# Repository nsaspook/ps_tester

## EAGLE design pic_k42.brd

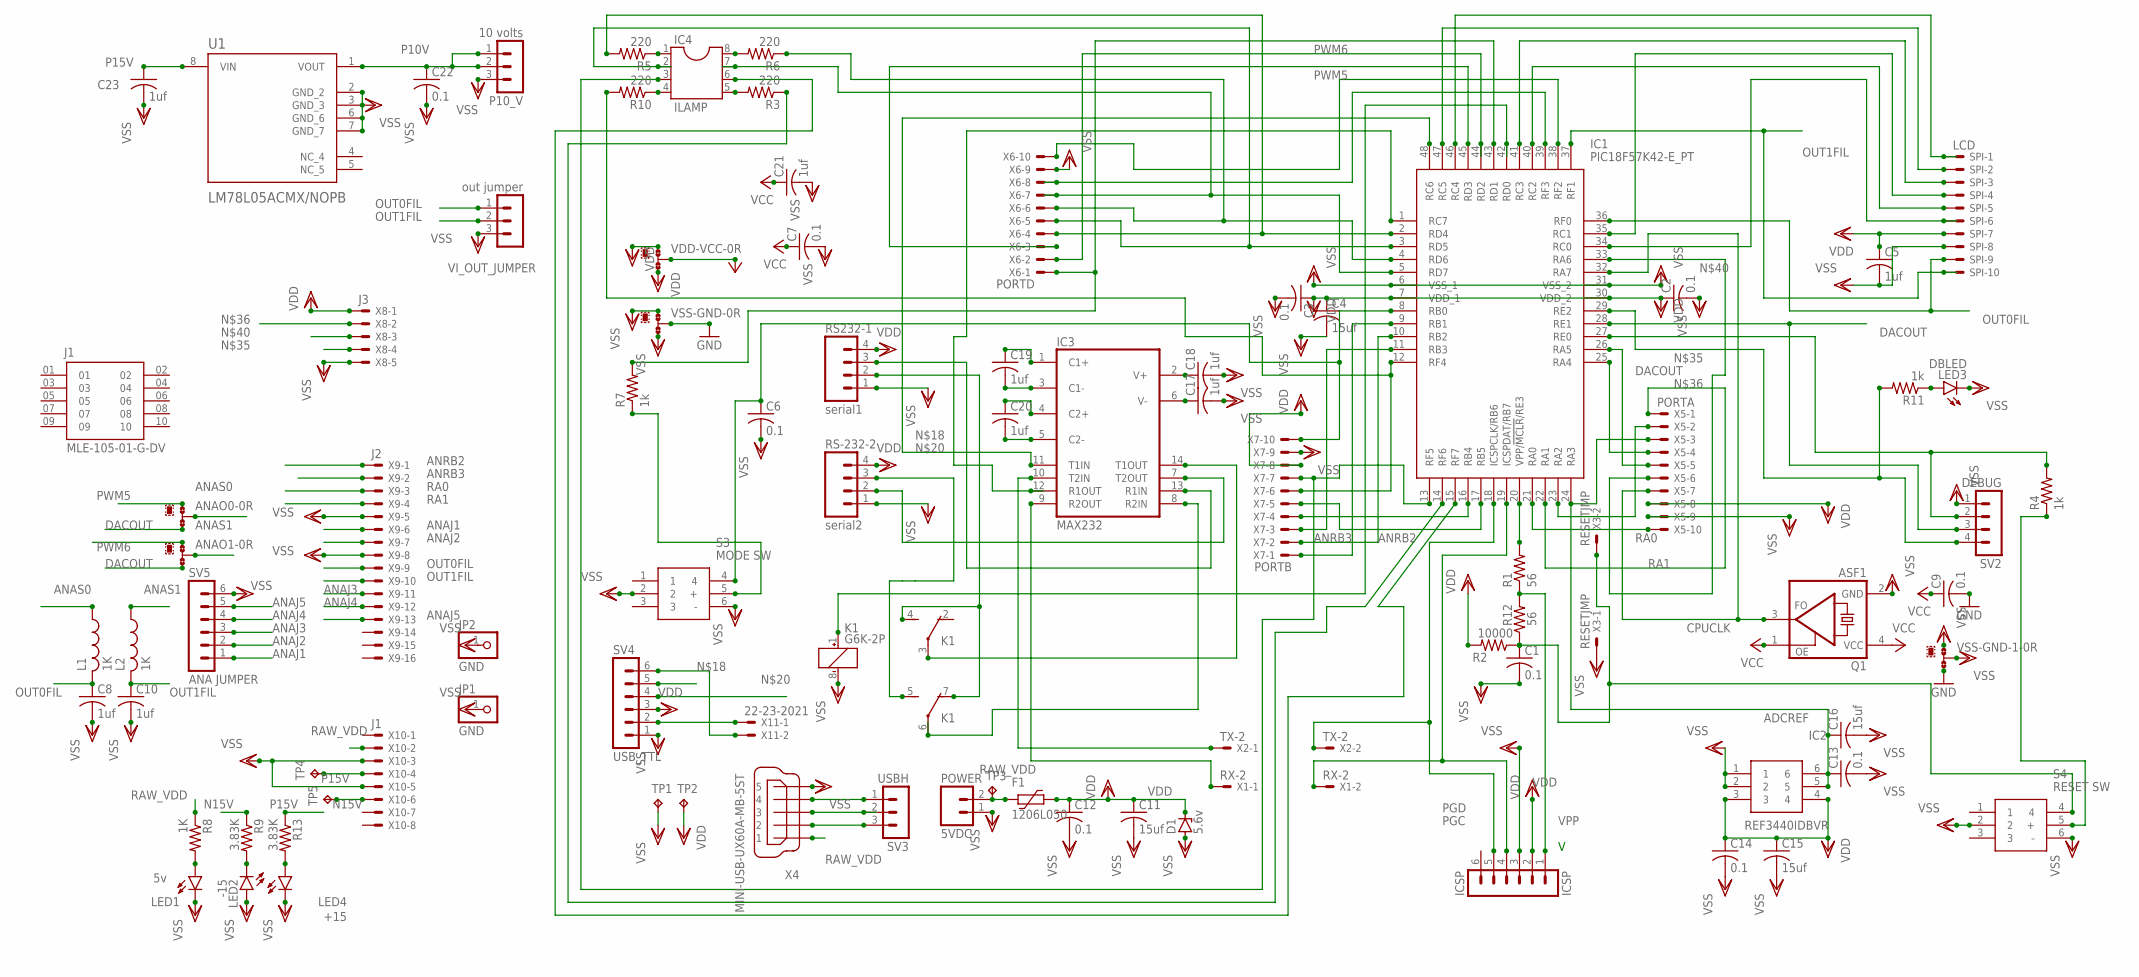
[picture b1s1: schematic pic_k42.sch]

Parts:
ANAO0: PS V; A0R-JMP
ANAO1: PS I; A0R-JMP
C1, C2, C3, C6, C7, C9, C12, C13, C14, C22: 0.1; C1206
C4, C11, C15, C16: 15uf; C1206
C5, C8, C10, C17, C18, C19, C20, C21, C23: 1uf; C0805
D1: 5.6v; DO34Z7
F1: 1206L050; 1206L
IC1: PIC18F57K42-E_PT; QFP50P900X900X120-48N
IC2: REF3440IDBVR; SOP95P280X145-6N
IC3: MAX232; DIL16
IC4: ILAMP; SOCKET-08
ICSP: ICSP; MA06-1
J1: MLE-105-01-G-DV; SAMTEC_MLE-105-01-G-DV
JP1, JP2: GND; 1X01
K1: G6K-2P
L1, L2: 1K; L2012C
LED1: 5v; CHIPLED_1206
LED2: -15; CHIPLED_1206
LED3: DBLED; CHIPLED_1206
LED4: +15; CHIPLED_1206
P10_V: 10 volts; MA03-1
POWER: 5VDC; 02P
Q1: ASF1; ASF
R1, R12: 56; R1206
R2: 10000; R1206
R3, R5, R6, R10: 220; R1206
R4, R7, R11: 1k; R1206
R8: 1K; R1206
R9, R13: 3.83K; R1206
RS232-1: serial1; 04P
RS-232-2: serial2; 04P
S3: MODE SW; B3W-9_1-LED
S4: RESET SW; B3W-9_1-LED
SPI: LCD; 22-23-2101
SV2: DEBUG; MA04-1
SV3: USBH; MA03-1
SV4: USB_TTL; MA06-1
SV5: ANA JUMPER; MA06-1
TP1, TP2, TP3, TP4, TP5: TPB1,27; B1,27
U1: LM78L05ACMX/NOPB; SOIC127P599X175-8N
VDD-VCC: VDD-VCC; A0R-JMP
VI_OUT_JUMPER: out jumper; MA03-1
VSS-GND: VSS-GND; A0R-JMP
VSS-GND-1: 0R-JUMPA; A0R-JMP
X1: RX-2; 332-02
X2: TX-2; 332-02
X3: RESETJMP; 332-02
X4: MINI-USB-UX60A-MB-5ST; UX60A-MB-5ST
X5: PORTA; 22-23-2101
X6: PORTD; 22-23-2101
X7: PORTB; 22-23-2101
X8: J3; KK-156-5
X9: J2; KK-156-16
X10: J1; KK-156-8
X11: 22-23-2021

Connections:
ADCREF: C13.1, C16.1, IC1.24 (RA3), IC2.5, IC2.6, X5.3
ANAJ1: SV5.1, X9.6
ANAJ2: SV5.2, X9.7
ANAJ3: SV5.3, X9.11
ANAJ4: SV5.4, X9.12
ANAJ5: SV5.5, X9.13
ANAS0: ANAO0.2, L1.1
ANAS1: ANAO1.2, L2.1
ANRB2: IC1.10 (RB2), X7.2, X9.1
ANRB3: IC1.11 (RB3), X7.3, X9.2
CPUCLK: IC1.32 (RA7), Q1.3 (FO), X5.7
DACOUT: ANAO0.3, ANAO1.3, IC1.23 (RA2), IC1.28 (RE1), SV2.3, X5.2
GND: C9.2, IC3.15 (GND), VSS-GND.2, VSS-GND-1.3
N15V: R9.1, TP5.TP, X10.6
unnamed: IC1.20 (VPP/!MCLR!/RE3), R1.2
unnamed: IC4.1, R5.1
unnamed: C17.1, IC3.6 (V-)
unnamed: C18.1, IC3.2 (V+)
unnamed: C19.1, IC3.1 (C1+)
unnamed: C20.1, IC3.4 (C2+)
unnamed: C20.2, IC3.5 (C2-)
unnamed: C19.2, IC3.3 (C1-)
unnamed: K1.4 (S), K1.7 (O), RS232-1.2
unnamed: IC3.7 (T2OUT), RS-232-2.2
unnamed: IC3.13 (R1IN), RS232-1.3
unnamed: IC4.8, R6.2
unnamed: IC1.1 (RC7), IC3.12 (R1OUT), SV4.5
unnamed: IC3.9 (R2OUT), X1.1
unnamed: IC1.48 (RC6), IC3.11 (T1IN), SV4.4
unnamed: R4.1, S4.5 (+)
unnamed: IC3.10 (T2IN), X2.1
unnamed: IC1.27 (RE0), R4.2, SV2.2
unnamed: IC1.29 (RE2), R11.2, SV2.4
unnamed: IC3.14 (T1OUT), K1.3
unnamed: IC3.8 (R2IN), K1.6
unnamed: IC1.42 (RD0), K1.1 (+)
unnamed: IC1.46 (RC4), SPI.1
unnamed: IC1.47 (RC5), SPI.2
unnamed: IC1.41 (RC3), SPI.3
unnamed: IC1.35 (RC1), SPI.4
unnamed: IC1.40 (RC2), SPI.5
unnamed: IC1.34 (RC0), SPI.6
unnamed: IC1.26 (RA5), X5.5, X8.4
unnamed: IC1.25 (RA4), X5.4, X8.2
unnamed: IC1.33 (RA6), X5.6, X8.3
unnamed: C6.1, IC1.8 (RB0), S3.4, X7.10
unnamed: IC1.45 (RD3), X6.3
unnamed: IC1.2 (RD4), R5.2, X6.4
unnamed: IC1.3 (RD5), IC4.2, X6.5
unnamed: IC1.4 (RD6), R6.1, X6.6
unnamed: IC1.5 (RD7), IC4.7, X6.7
unnamed: IC1.39 (RF3), X6.8
unnamed: IC1.43 (RD1), R7.2, X6.1
unnamed: IC1.9 (RB1), X7.1
unnamed: IC4.5, R3.2
unnamed: IC1.16 (RB4), X7.4
unnamed: IC1.17 (RB5), X7.5
unnamed: IC1.12 (RF4), R10.2, X7.6
unnamed: IC1.13 (RF5), IC4.3, X7.7
unnamed: IC1.15 (RF7), IC4.6
unnamed: IC1.14 (RF6), R3.1
unnamed: K1.5 (S), RS-232-2.3
unnamed: IC4.4, R10.1
unnamed: R7.1, S3.5 (+)
unnamed: LED3.A, R11.1
unnamed: SV3.1, X4.4
unnamed: SV3.2, X4.3
unnamed: SV3.3, X4.2
unnamed: C1.1, R2.1, R12.1, S4.4, X3.2
unnamed: SV4.6, X11.2
unnamed: SV4.2, X11.1
unnamed: LED1.A, R8.2
unnamed: LED2.C, R9.2
unnamed: LED4.A, R13.2
NC_4: U1.4 (NC_4)
NC_5: U1.5 (NC_5)
OUT0FIL: C8.1, IC1.36 (RF0), L1.2, SPI.9, VI_OUT_JUMPER.1, X9.9
OUT1FIL: C10.1, IC1.37 (RF1), L2.2, SPI.10, VI_OUT_JUMPER.2, X9.10
P10V: C22.1, P10_V.1, P10_V.2, U1.1 (VOUT)
P15V: C23.1, R13.1, TP4.TP, U1.8 (VIN), X10.4
PGC: IC1.18 (ICSPCLK/RB6), ICSP.5, X2.2
PGD: IC1.19 (ICSPDAT/RB7), ICSP.4, X1.2
PWM5: ANAO0.1, IC1.38 (RF2), X6.10
PWM6: ANAO1.1, IC1.44 (RD2), X6.2
RA0: IC1.21 (RA0), X5.10, X9.3
RA1: IC1.22 (RA1), X5.1, X9.4
RAW_VDD: F1.2, POWER.2, R8.1, TP3.TP, X4.1, X10.2
VCC: C7.1, C9.1, C21.1, IC3.16 (VCC), Q1.1 (OE), Q1.4 (VCC), VDD-VCC.2
VDD: C2.1, C3.1, C4.1, C5.1, C11.1, C12.1, C14.1, C15.1, D1.C, F1.1, IC1.7 (VDD_1), IC1.30 (VDD_2), IC2.3, IC2.4, ICSP.2, R2.2, RS232-1.4, RS-232-2.4, SPI.7, SV4.3, TP2.TP, VDD-VCC.1, VDD-VCC.3, X5.8, X7.8, X8.1
VPP: ICSP.1, R1.1, R12.2
VSS: C1.2, C2.2, C3.2, C4.2, C5.2, C6.2, C7.2, C8.2, C10.2, C11.2, C12.2, C13.2, C14.2, C15.2, C16.2, C17.2, C18.2, C21.2, C22.2, C23.2, D1.A, IC1.6 (VSS_1), IC1.31 (VSS_2), IC2.1, IC2.2, ICSP.3, JP1.1, JP2.1, K1.8 (-), LED1.C, LED2.A, LED3.C, LED4.C, P10_V.3, POWER.1, Q1.2 (GND), RS232-1.1, RS-232-2.1, S3.2, S3.6 (-), S4.2, S4.6 (-), SPI.8, SV2.1, SV4.1, SV5.6, TP1.TP, U1.2 (GND_2), U1.3 (GND_3), U1.6 (GND_6), U1.7 (GND_7), VI_OUT_JUMPER.3, VSS-GND.1, VSS-GND.3, VSS-GND-1.1, VSS-GND-1.2, X3.1, X4.5, X5.9, X6.9, X7.9, X8.5, X9.5, X9.8, X10.3, X10.5

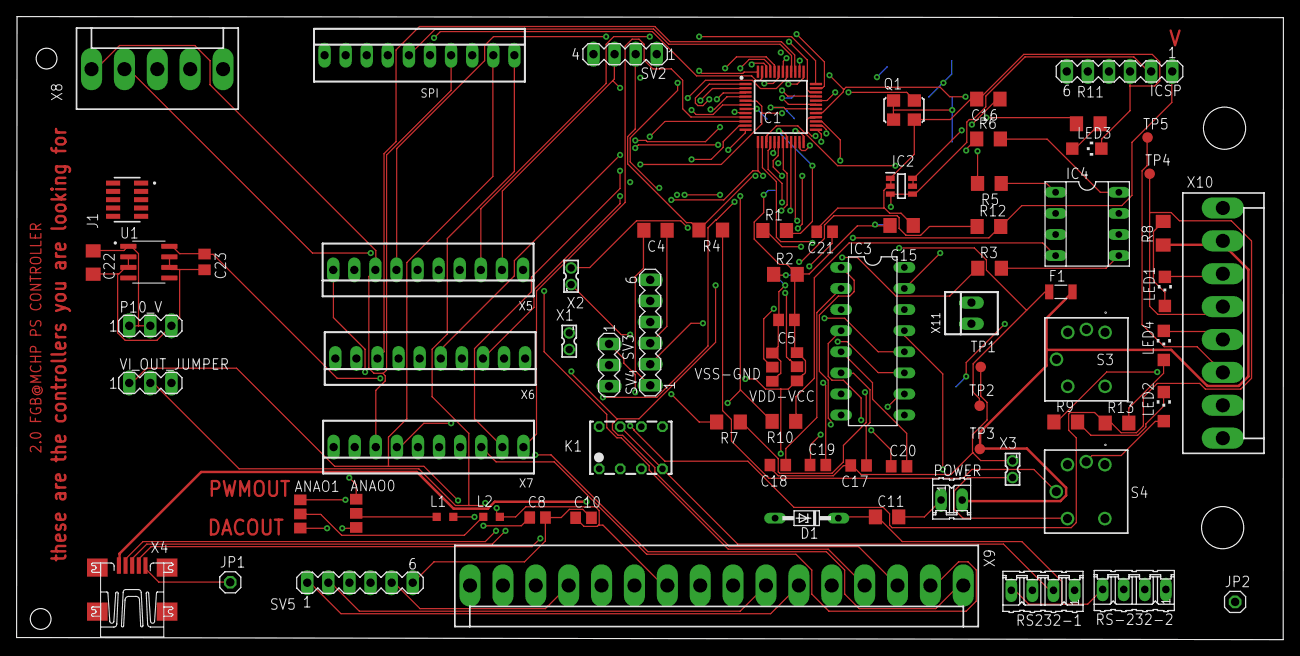
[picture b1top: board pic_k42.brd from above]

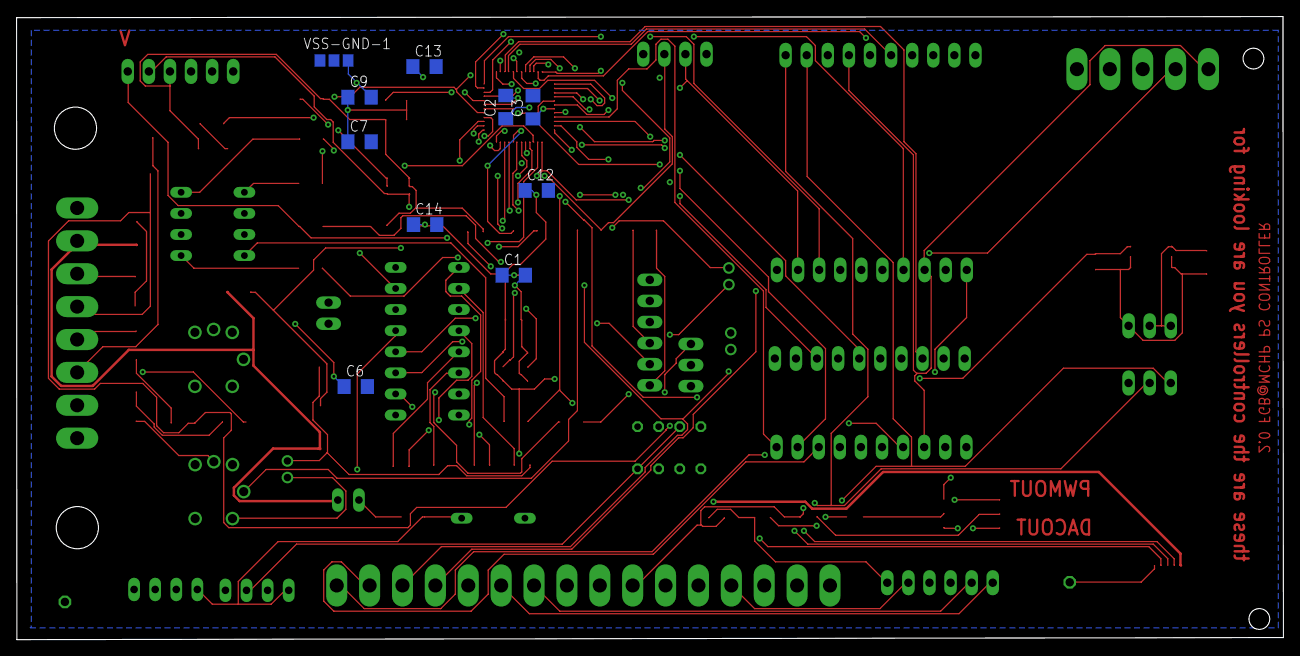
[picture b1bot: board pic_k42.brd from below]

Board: 4 copper layers, 152.6 x 75.0 mm, 88 parts (10 on the bottom side), 89 nets.

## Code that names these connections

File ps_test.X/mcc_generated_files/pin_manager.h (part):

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// get/set PS_V_ANA_S aliases
#define PS_V_ANA_S_TRIS                 TRISAbits.TRISA0
#define PS_V_ANA_S_LAT                  LATAbits.LATA0
#define PS_V_ANA_S_PORT                 PORTAbits.RA0
#define PS_V_ANA_S_WPU                  WPUAbits.WPUA0
#define PS_V_ANA_S_OD                   ODCONAbits.ODCA0
#define PS_V_ANA_S_ANS                  ANSELAbits.ANSELA0
#define PS_V_ANA_S_SetHigh()            do { LATAbits.LATA0 = 1; } while(0)
#define PS_V_ANA_S_SetLow()             do { LATAbits.LATA0 = 0; } while(0)
#define PS_V_ANA_S_Toggle()             do { LATAbits.LATA0 = ~LATAbits.LATA0; } while(0)
#define PS_V_ANA_S_GetValue()           PORTAbits.RA0
#define PS_V_ANA_S_SetDigitalInput()    do { TRISAbits.TRISA0 = 1; } while(0)
#define PS_V_ANA_S_SetDigitalOutput()   do { TRISAbits.TRISA0 = 0; } while(0)
#define PS_V_ANA_S_SetPullup()          do { WPUAbits.WPUA0 = 1; } while(0)
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// get/set PS_I_ANA_S aliases
#define PS_I_ANA_S_TRIS                 TRISAbits.TRISA1
#define PS_I_ANA_S_LAT                  LATAbits.LATA1
#define PS_I_ANA_S_PORT                 PORTAbits.RA1
#define PS_I_ANA_S_WPU                  WPUAbits.WPUA1
#define PS_I_ANA_S_OD                   ODCONAbits.ODCA1
#define PS_I_ANA_S_ANS                  ANSELAbits.ANSELA1
#define PS_I_ANA_S_SetHigh()            do { LATAbits.LATA1 = 1; } while(0)
#define PS_I_ANA_S_SetLow()             do { LATAbits.LATA1 = 0; } while(0)
#define PS_I_ANA_S_Toggle()             do { LATAbits.LATA1 = ~LATAbits.LATA1; } while(0)
#define PS_I_ANA_S_GetValue()           PORTAbits.RA1
#define PS_I_ANA_S_SetDigitalInput()    do { TRISAbits.TRISA1 = 1; } while(0)
#define PS_I_ANA_S_SetDigitalOutput()   do { TRISAbits.TRISA1 = 0; } while(0)
#define PS_I_ANA_S_SetPullup()          do { WPUAbits.WPUA1 = 1; } while(0)
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#define RA2_SetHigh()            do { LATAbits.LATA2 = 1; } while(0)
#define RA2_SetLow()             do { LATAbits.LATA2 = 0; } while(0)
#define RA2_Toggle()             do { LATAbits.LATA2 = ~LATAbits.LATA2; } while(0)
#define RA2_GetValue()              PORTAbits.RA2
#define RA2_SetDigitalInput()    do { TRISAbits.TRISA2 = 1; } while(0)
#define RA2_SetDigitalOutput()   do { TRISAbits.TRISA2 = 0; } while(0)
#define RA2_SetPullup()             do { WPUAbits.WPUA2 = 1; } while(0)
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#define RA3_SetHigh()            do { LATAbits.LATA3 = 1; } while(0)
#define RA3_SetLow()             do { LATAbits.LATA3 = 0; } while(0)
#define RA3_Toggle()             do { LATAbits.LATA3 = ~LATAbits.LATA3; } while(0)
#define RA3_GetValue()              PORTAbits.RA3
#define RA3_SetDigitalInput()    do { TRISAbits.TRISA3 = 1; } while(0)
#define RA3_SetDigitalOutput()   do { TRISAbits.TRISA3 = 0; } while(0)
#define RA3_SetPullup()             do { WPUAbits.WPUA3 = 1; } while(0)
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// get/set HVON_IN_RA4 aliases
#define HVON_IN_RA4_TRIS                 TRISAbits.TRISA4
#define HVON_IN_RA4_LAT                  LATAbits.LATA4
#define HVON_IN_RA4_PORT                 PORTAbits.RA4
#define HVON_IN_RA4_WPU                  WPUAbits.WPUA4
#define HVON_IN_RA4_OD                   ODCONAbits.ODCA4
#define HVON_IN_RA4_ANS                  ANSELAbits.ANSELA4
#define HVON_IN_RA4_SetHigh()            do { LATAbits.LATA4 = 1; } while(0)
#define HVON_IN_RA4_SetLow()             do { LATAbits.LATA4 = 0; } while(0)
#define HVON_IN_RA4_Toggle()             do { LATAbits.LATA4 = ~LATAbits.LATA4; } while(0)
#define HVON_IN_RA4_GetValue()           PORTAbits.RA4
#define HVON_IN_RA4_SetDigitalInput()    do { TRISAbits.TRISA4 = 1; } while(0)
#define HVON_IN_RA4_SetDigitalOutput()   do { TRISAbits.TRISA4 = 0; } while(0)
#define HVON_IN_RA4_SetPullup()          do { WPUAbits.WPUA4 = 1; } while(0)
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// get/set HVON_OUT_RA5 aliases
#define HVON_OUT_RA5_TRIS                 TRISAbits.TRISA5
#define HVON_OUT_RA5_LAT                  LATAbits.LATA5
#define HVON_OUT_RA5_PORT                 PORTAbits.RA5
#define HVON_OUT_RA5_WPU                  WPUAbits.WPUA5
#define HVON_OUT_RA5_OD                   ODCONAbits.ODCA5
#define HVON_OUT_RA5_ANS                  ANSELAbits.ANSELA5
#define HVON_OUT_RA5_SetHigh()            do { LATAbits.LATA5 = 1; } while(0)
#define HVON_OUT_RA5_SetLow()             do { LATAbits.LATA5 = 0; } while(0)
#define HVON_OUT_RA5_Toggle()             do { LATAbits.LATA5 = ~LATAbits.LATA5; } while(0)
#define HVON_OUT_RA5_GetValue()           PORTAbits.RA5
#define HVON_OUT_RA5_SetDigitalInput()    do { TRISAbits.TRISA5 = 1; } while(0)
#define HVON_OUT_RA5_SetDigitalOutput()   do { TRISAbits.TRISA5 = 0; } while(0)
#define HVON_OUT_RA5_SetPullup()          do { WPUAbits.WPUA5 = 1; } while(0)
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// get/set OVERLOAD aliases
#define OVERLOAD_TRIS                 TRISAbits.TRISA6
#define OVERLOAD_LAT                  LATAbits.LATA6
#define OVERLOAD_PORT                 PORTAbits.RA6
#define OVERLOAD_WPU                  WPUAbits.WPUA6
#define OVERLOAD_OD                   ODCONAbits.ODCA6
#define OVERLOAD_ANS                  ANSELAbits.ANSELA6
#define OVERLOAD_SetHigh()            do { LATAbits.LATA6 = 1; } while(0)
#define OVERLOAD_SetLow()             do { LATAbits.LATA6 = 0; } while(0)
#define OVERLOAD_Toggle()             do { LATAbits.LATA6 = ~LATAbits.LATA6; } while(0)
#define OVERLOAD_GetValue()           PORTAbits.RA6
#define OVERLOAD_SetDigitalInput()    do { TRISAbits.TRISA6 = 1; } while(0)
#define OVERLOAD_SetDigitalOutput()   do { TRISAbits.TRISA6 = 0; } while(0)
#define OVERLOAD_SetPullup()          do { WPUAbits.WPUA6 = 1; } while(0)
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// get/set MODESW_RB0 aliases
#define MODESW_RB0_TRIS                 TRISBbits.TRISB0
#define MODESW_RB0_LAT                  LATBbits.LATB0
#define MODESW_RB0_PORT                 PORTBbits.RB0
#define MODESW_RB0_WPU                  WPUBbits.WPUB0
#define MODESW_RB0_OD                   ODCONBbits.ODCB0
#define MODESW_RB0_ANS                  ANSELBbits.ANSELB0
#define MODESW_RB0_SetHigh()            do { LATBbits.LATB0 = 1; } while(0)
#define MODESW_RB0_SetLow()             do { LATBbits.LATB0 = 0; } while(0)
#define MODESW_RB0_Toggle()             do { LATBbits.LATB0 = ~LATBbits.LATB0; } while(0)
#define MODESW_RB0_GetValue()           PORTBbits.RB0
#define MODESW_RB0_SetDigitalInput()    do { TRISBbits.TRISB0 = 1; } while(0)
#define MODESW_RB0_SetDigitalOutput()   do { TRISBbits.TRISB0 = 0; } while(0)
#define MODESW_RB0_SetPullup()          do { WPUBbits.WPUB0 = 1; } while(0)
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// get/set PS_V_ANA aliases
#define PS_V_ANA_TRIS                 TRISBbits.TRISB2
#define PS_V_ANA_LAT                  LATBbits.LATB2
#define PS_V_ANA_PORT                 PORTBbits.RB2
#define PS_V_ANA_WPU                  WPUBbits.WPUB2
#define PS_V_ANA_OD                   ODCONBbits.ODCB2
#define PS_V_ANA_ANS                  ANSELBbits.ANSELB2
#define PS_V_ANA_SetHigh()            do { LATBbits.LATB2 = 1; } while(0)
#define PS_V_ANA_SetLow()             do { LATBbits.LATB2 = 0; } while(0)
#define PS_V_ANA_Toggle()             do { LATBbits.LATB2 = ~LATBbits.LATB2; } while(0)
#define PS_V_ANA_GetValue()           PORTBbits.RB2
#define PS_V_ANA_SetDigitalInput()    do { TRISBbits.TRISB2 = 1; } while(0)
#define PS_V_ANA_SetDigitalOutput()   do { TRISBbits.TRISB2 = 0; } while(0)
#define PS_V_ANA_SetPullup()          do { WPUBbits.WPUB2 = 1; } while(0)
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// get/set PS_I_ANA aliases
#define PS_I_ANA_TRIS                 TRISBbits.TRISB3
#define PS_I_ANA_LAT                  LATBbits.LATB3
#define PS_I_ANA_PORT                 PORTBbits.RB3
#define PS_I_ANA_WPU                  WPUBbits.WPUB3
#define PS_I_ANA_OD                   ODCONBbits.ODCB3
#define PS_I_ANA_ANS                  ANSELBbits.ANSELB3
#define PS_I_ANA_SetHigh()            do { LATBbits.LATB3 = 1; } while(0)
#define PS_I_ANA_SetLow()             do { LATBbits.LATB3 = 0; } while(0)
#define PS_I_ANA_Toggle()             do { LATBbits.LATB3 = ~LATBbits.LATB3; } while(0)
#define PS_I_ANA_GetValue()           PORTBbits.RB3
#define PS_I_ANA_SetDigitalInput()    do { TRISBbits.TRISB3 = 1; } while(0)
#define PS_I_ANA_SetDigitalOutput()   do { TRISBbits.TRISB3 = 0; } while(0)
#define PS_I_ANA_SetPullup()          do { WPUBbits.WPUB3 = 1; } while(0)
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// get/set channel_ANB4 aliases
#define channel_ANB4_TRIS                 TRISBbits.TRISB4
#define channel_ANB4_LAT                  LATBbits.LATB4
#define channel_ANB4_PORT                 PORTBbits.RB4
#define channel_ANB4_WPU                  WPUBbits.WPUB4
#define channel_ANB4_OD                   ODCONBbits.ODCB4
#define channel_ANB4_ANS                  ANSELBbits.ANSELB4
#define channel_ANB4_SetHigh()            do { LATBbits.LATB4 = 1; } while(0)
#define channel_ANB4_SetLow()             do { LATBbits.LATB4 = 0; } while(0)
#define channel_ANB4_Toggle()             do { LATBbits.LATB4 = ~LATBbits.LATB4; } while(0)
#define channel_ANB4_GetValue()           PORTBbits.RB4
#define channel_ANB4_SetDigitalInput()    do { TRISBbits.TRISB4 = 1; } while(0)
#define channel_ANB4_SetDigitalOutput()   do { TRISBbits.TRISB4 = 0; } while(0)
#define channel_ANB4_SetPullup()          do { WPUBbits.WPUB4 = 1; } while(0)
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
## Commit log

2022-02-16 K42 PS controller emulator
2024-07-15 Revert "up"
    This reverts commit f639369d4aa6de1d8af3c26b48df687186b46926.
2024-07-15 Revert "up"
    This reverts commit 2af174bc1ac14fa5ed8294ec6c26e2dbc3c0e6fd.
2024-07-15 Revert "up"
    This reverts commit 290ed4c0a427a779eceb4632a7636d3bedebf2e6.

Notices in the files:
ps_test.X/mcc_generated_files/pin_manager.h:
(c) 2018 Microchip Technology Inc. and its subsidiaries.
